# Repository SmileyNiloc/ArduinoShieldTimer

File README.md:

This is the repository to house the project files for an Arduino Shield that was designed to function as a cloud synced timer with adafruit.
The file "Colin Aten - Timer IoT device report.pdf" contains most of the information about the project.

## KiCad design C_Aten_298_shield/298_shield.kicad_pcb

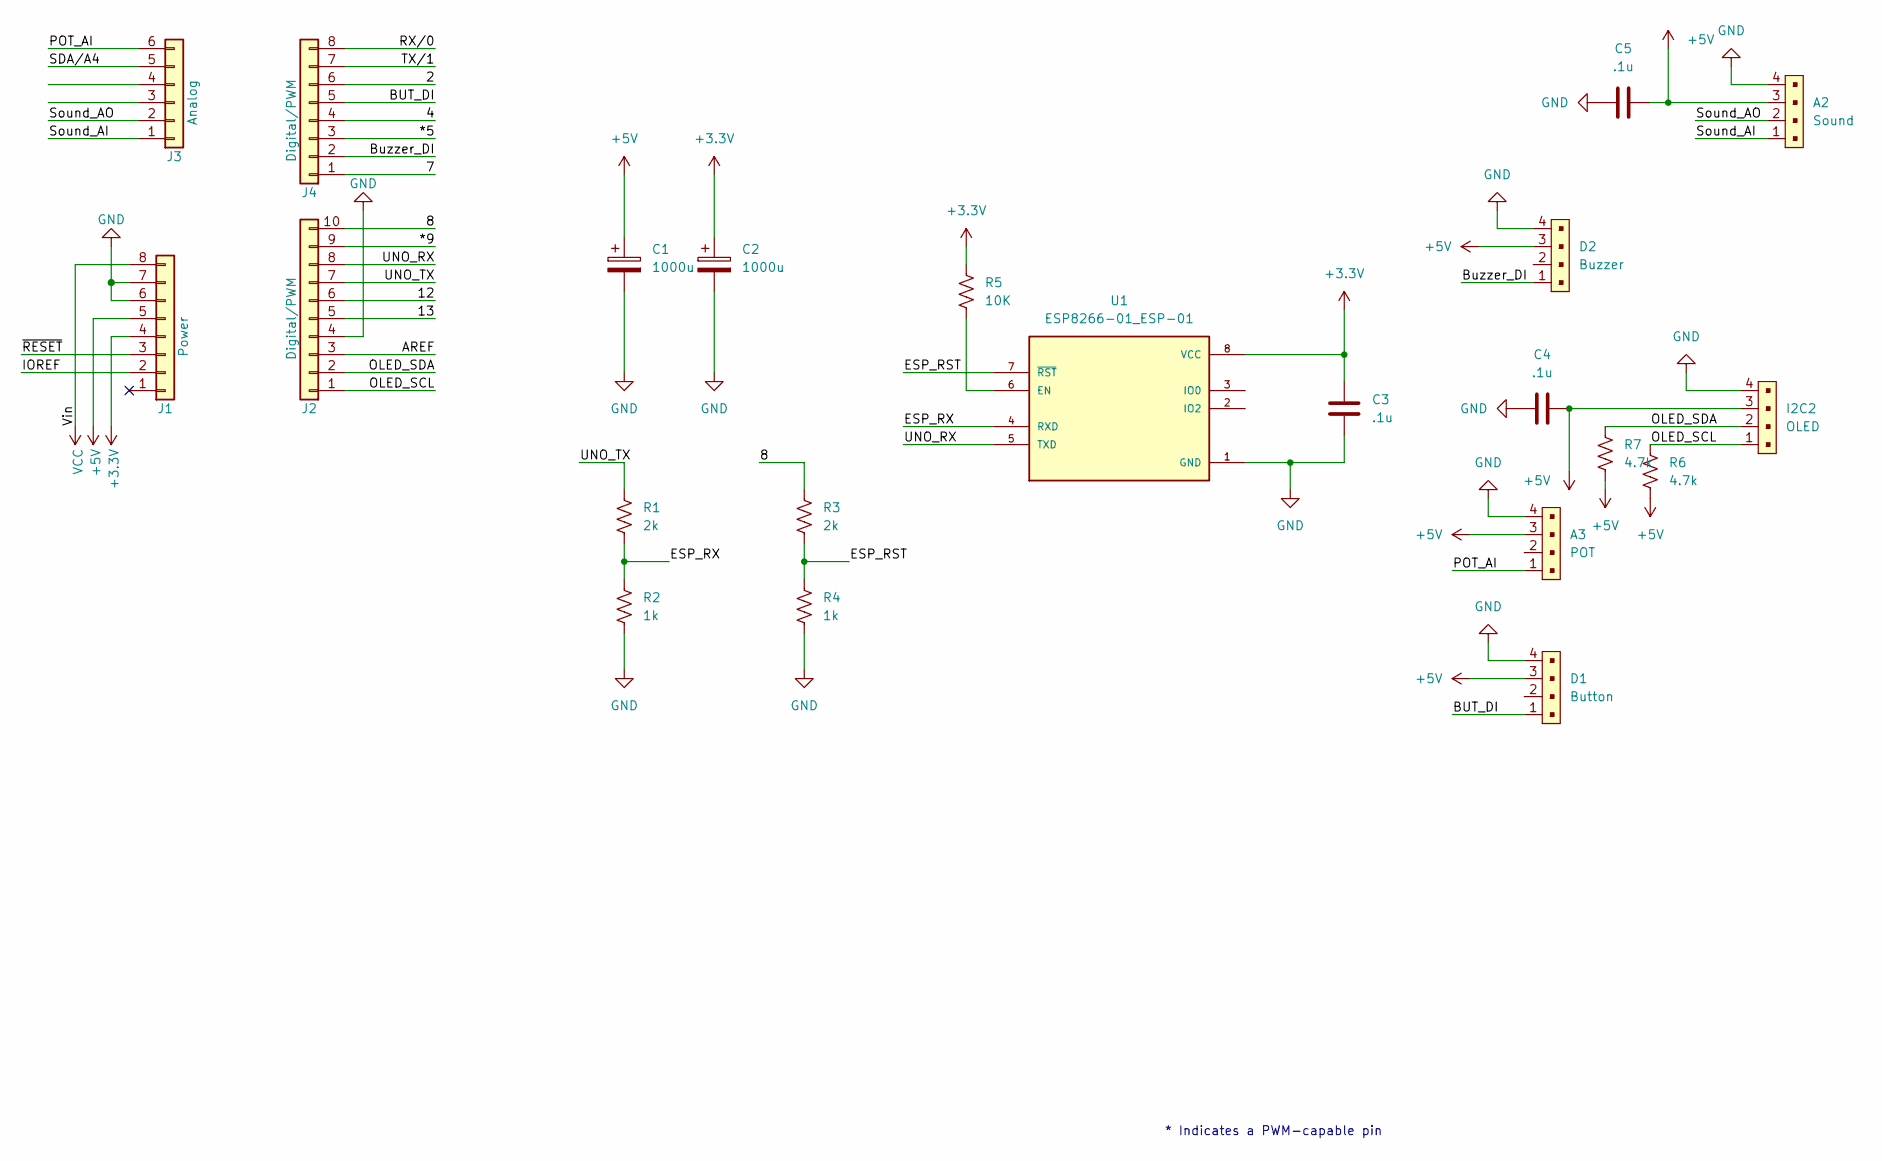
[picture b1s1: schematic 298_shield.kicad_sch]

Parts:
A2: Sound; PinHeader_1x4_P2mm_Drill1mm; MPN B4B-PH-K-S(LF)(SN)
A3: POT; PinHeader_1x4_P2mm_Drill1mm; MPN B4B-PH-K-S(LF)(SN)
C1, C2: 1000u; CP_Radial_D10.0mm_P5.00mm
C3, C4, C5: .1u
D1: Button; PinHeader_1x4_P2mm_Drill1mm; MPN B4B-PH-K-S(LF)(SN)
D2: Buzzer; PinHeader_1x4_P2mm_Drill1mm; MPN B4B-PH-K-S(LF)(SN)
I2C2: OLED; PinHeader_1x4_P2mm_Drill1mm; MPN B4B-PH-K-S(LF)(SN)
J1: Power; PinSocket_1x08_P2.54mm_Vertical
J2: Digital/PWM; PinSocket_1x10_P2.54mm_Vertical
J3: Analog; PinSocket_1x06_P2.54mm_Vertical
J4: Digital/PWM; PinSocket_1x08_P2.54mm_Vertical
R1, R3: 2k; R_Axial_DIN0207_L6.3mm_D2.5mm_P10.16mm_Horizontal
R2, R4: 1k; R_Axial_DIN0207_L6.3mm_D2.5mm_P10.16mm_Horizontal
R5: 10K; R_Axial_DIN0207_L6.3mm_D2.5mm_P10.16mm_Horizontal
R6, R7: 4.7k; R_Axial_DIN0207_L6.3mm_D2.5mm_P10.16mm_Horizontal
U1: ESP8266-01_ESP-01; XCVR_ESP8266-01_ESP-01; PARTREV V1.2

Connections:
+3.3V: C2.1, C3.1, J1.4, R5.1, U1.8 (VCC)
+5V: A2.3, A3.3, C1.1, C4.2, C5.2, D1.3, D2.3, I2C2.3, J1.5, R6.2, R7.2; also elsewhere on the board
/2: J4.6
/4: J4.4
/7: J4.1
/8: J2.10, R3.1
/12: J2.6
/13: J2.5
/*5: J4.3
/*9: J2.9
/AREF: J2.3
/BUT_DI: D1.1, J4.5
/Buzzer_DI: D2.1, J4.2
/ESP_RST: R3.2, R4.1, U1.7 (~RST)
/ESP_RX: R1.2, R2.1, U1.4 (RXD)
/IOREF: J1.2
/OLED_SCL: I2C2.1, J2.1, R6.1
/OLED_SDA: I2C2.2, J2.2, R7.1
/POT_AI: A3.1, J3.6
/RX/0: J4.8
/SDA/A4: J3.5
/Sound_AI: A2.1, J3.1; also elsewhere on the board
/Sound_AO: A2.2, J3.2; also elsewhere on the board
/TX/1: J4.7
/UNO_RX: J2.8, U1.5 (TXD)
/UNO_TX: J2.7, R1.1
/~RESET: J1.3
GND: A2.4, A3.4, C1.2, C2.2, C3.2, C4.1, C5.1, D1.4, D2.4, I2C2.4, J1.6, J1.7, J2.4, R2.2, R4.2, U1.1 (GND)
unnamed: R5.2, U1.6 (EN)
VCC: J1.8

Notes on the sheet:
* Indicates a PWM-capable pin

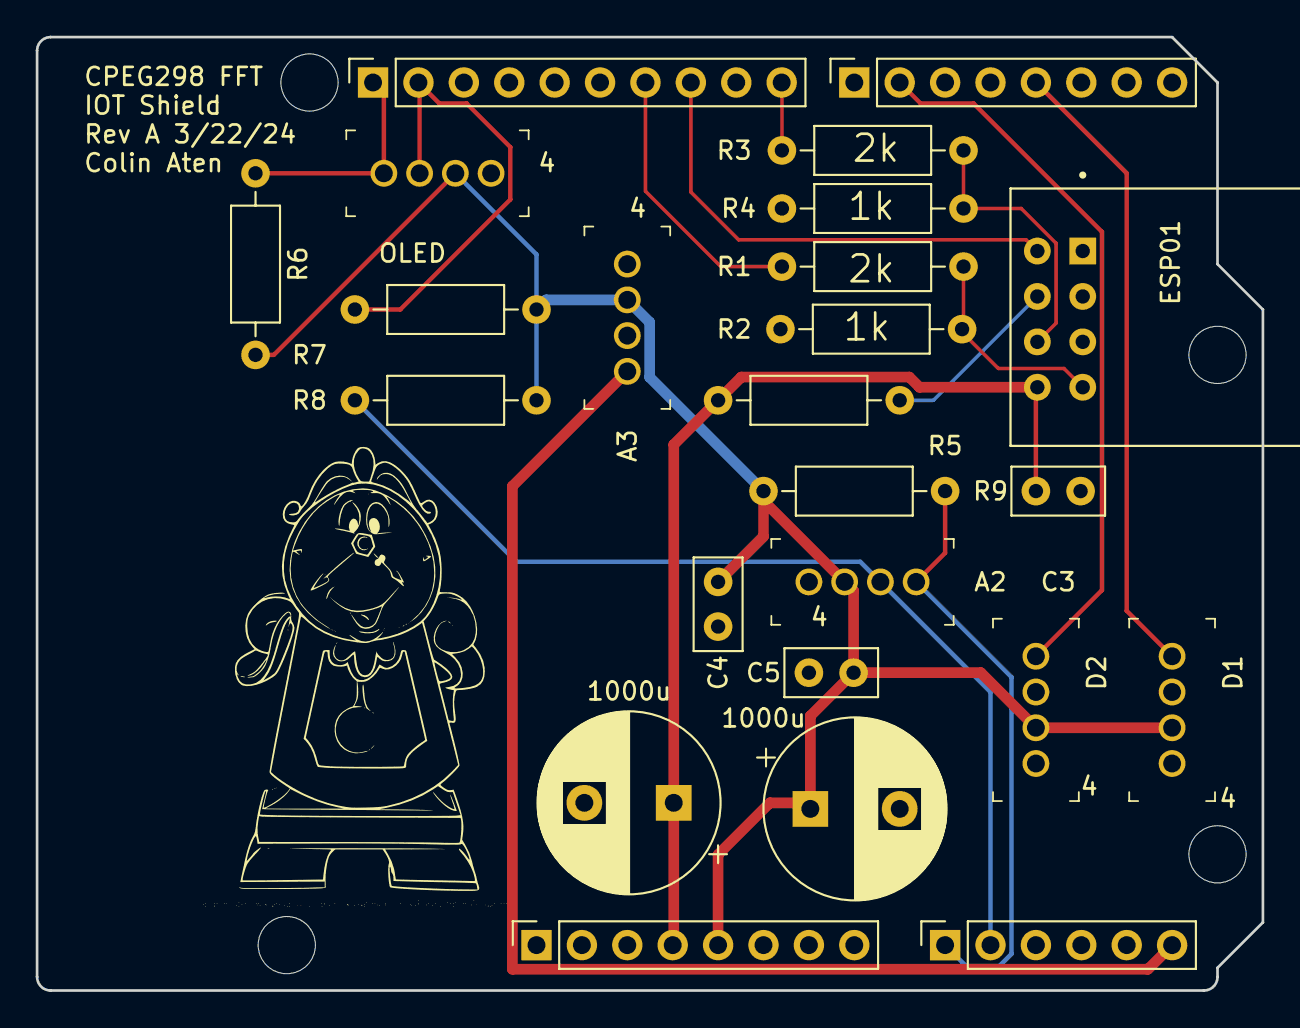
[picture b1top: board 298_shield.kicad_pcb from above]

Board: 2 copper layers, 68.6 x 53.3 mm, 28 parts (0 on the bottom side), 16 nets.

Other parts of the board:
MH1, MH2, MH3, MH4: MountingHole_3.2mm
R8, R9: 4.7k; R_Axial_DIN0207_L6.3mm_D2.5mm_P10.16mm_Horizontal

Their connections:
+5V: R8.2, R9.2; also elsewhere on the board
/Sound_AI: R9.1; also elsewhere on the board
/Sound_AO: R8.1; also elsewhere on the board

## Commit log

2024-11-03 Add Project Files for Arduino Shield
